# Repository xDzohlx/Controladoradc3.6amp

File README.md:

# Controladoradc3.6amp
Controladora electronica de velocidad de 3.6 amperios hasta 25 volts V1.1
Controladora electronica de velocidad de 3.6 amperios hasta 25 volts V1.1 Esta es la versión 1.1 de la tarjeta controladora fue diseñada por Carlos Vega, la selección de componentes del driver y el microcontrolador por Aldo Bucio. Está basada en otra paca diseñada por Aldo bucio hace tiempo. Perdí el primer archivo de la placa pero estan los archivos gerber pero estan los de la version 1.1.

Especificaciones: 4 celdas de litio polímero, hasta 25 volts absolutos(por los capacitores de puede aumentar la tensión hasta 32 volts absolutos limitados por el regulador) 3.6 amperios por canal, protegida para más corriente se apaga y reinicia cuando se alcanza esta corriente. El driver de los motores es muy confiable y a prueba de balas lo que se necesita para el combate de robots Canales completamente mezclados para conducir un robot en modo diferencial. Se leen dos canales de pwm en cualquier protocolo de envío de 50 a 100 hz. También esta la version de firmware con lectura de ppm en un solo cable con decodificador de un canal para la activación de un servo u otro actuador. Los esquematicos y la placa estan diseñadas en Eagle.Fue programada en atmel studio 7 con el microcontrolador Attiny828.

Manual de operacion Caracteristicas

Gracias por usar la tarjeta controladora electrónica de velocidad. Características: Canal doble 3.6 A por canal Protección contra sobre corriente y sobre temperatura 2-6s de litio polímero 25 volts absolutos 7.2 Amp Canal doble Interfaz RC PWM, PPM Decodificador en modo PPM sin retraso. Canales mezclados o bidireccionales. Sin retraso de señal de radio Auto calibración al encendido BEC conmutada de alta eficiencia 88% 1 A hasta 2A continuos. (BEC) Respuesta lineal Adelante y atrás a máxima potencia. PWM de 32 Khz Freno del motor Tiempo de servicio muy largo puede estar encendida por más de 1 hr. Conector JST para batería. Conectores de servo para señales.

El modo de operación viene preprogramdo, como lectura independiente de PWM, PPM, mezclados, bidireccionales o canal sencillo de mayor corriente estos modos son el firmware de la controladora. Modo PWM. El canal 1 es el volate y el canal 2 es el acelerador, el primero controla los giros mientras que el segundo controla el acelerador y la reversa. Modo PPM. En el canal 1 se conecta la señal PPM, el canal 1 es el volante y el canal 2 es el acelerador. El cable del canal dos es un decodificador del canal 3. En cualquiera de los modos cuenta con auto calibración al encendido por lo que se tiene que dar un tiempo a esto de 5 segundos antes de mover cualquier valor del radiocontrol. El led muestra el estado de la controladora.
Un video probando la tarjeta: https://t.co/X4io4Tz9yK?amp=1

Otros videos arreglando issues:
https://youtube.com/live/U84N-yGLdbo?feature=share

https://youtube.com/live/5lfUKTcOBrQ?feature=share

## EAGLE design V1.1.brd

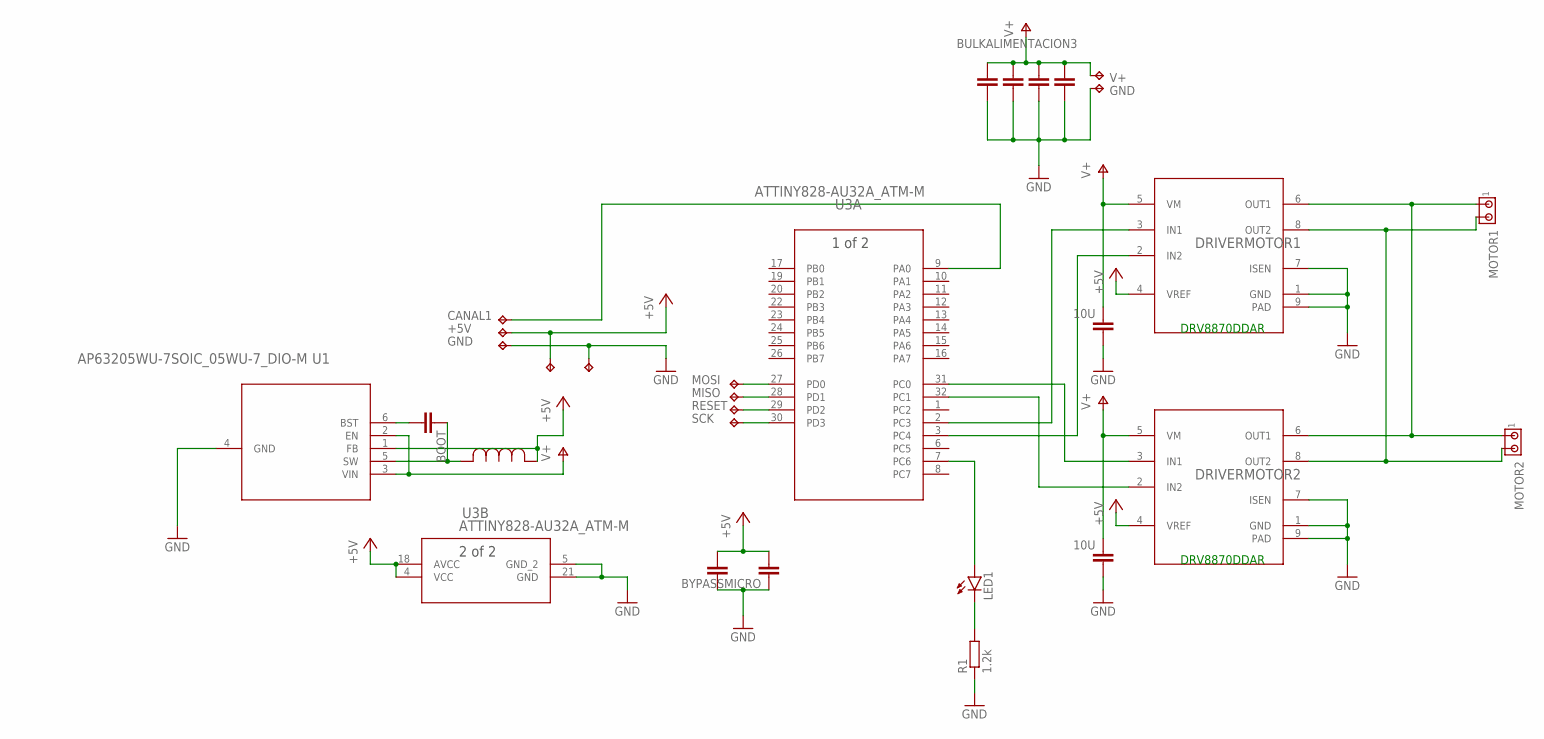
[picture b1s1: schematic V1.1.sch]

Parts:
BOOT: C-EUC0402; C0402
BULKALIMENTACION, BULKALIMENTACION1, BULKALIMENTACION2, BULKALIMENTACION3: C-EUC1206; C1206
BYPASS1: 10U; C0603
BYPASSMICRO, BYPASSMICRO2: C-EUC0603; C0603
BYPASSMOTOR2: 10U; C0603
DRIVERMOTOR1, DRIVERMOTOR2: DRV8870; DDA0008H_N
GND: TPTP20SQ; TP20SQ
LED1: LEDCHIPLED_0603; CHIPLED_0603
MISO: TPTP12R; TP12R
MOTOR1, MOTOR2: MTA02-100; 10X02MTA
R1: 1.2k; R0603
TP1, TP3, TP4, TP5, TP9: TPTP13SQ; TP13SQ
TP6, TP7, TP8: TPTP12R; TP12R
U1: AP63205WU-7SOIC_05WU-7_DIO-M; SOIC_05WU-7_DIO-M
U3: ATTINY828-AU32A_ATM-M; 32A_ATM-M
U$2: INDUCTOR4.7; IND_NRS5030T100MMGJ_TAY
V+: TPTP20SQ; TP20SQ

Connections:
+5V: BYPASSMICRO.2, BYPASSMICRO2.2, DRIVERMOTOR1.4 (VREF), DRIVERMOTOR2.4 (VREF), TP3.TP, TP9.TP, U1.1 (FB), U3.4 (VCC), U3.18 (AVCC), U$2.1
CANAL1: TP1.TP, U3.9 (PA0)
GND: BULKALIMENTACION.2, BULKALIMENTACION1.2, BULKALIMENTACION2.2, BULKALIMENTACION3.2, BYPASS1.1, BYPASSMICRO.1, BYPASSMICRO2.1, BYPASSMOTOR2.1, DRIVERMOTOR1.1 (GND), DRIVERMOTOR1.7 (ISEN), DRIVERMOTOR1.9 (PAD), DRIVERMOTOR2.1 (GND), DRIVERMOTOR2.7 (ISEN), DRIVERMOTOR2.9 (PAD), GND.TP, R1.1, TP4.TP, TP5.TP, U1.4 (GND), U3.5 (GND_2), U3.21 (GND)
MISO: TP6.TP, U3.28 (PD1)
MOSI: MISO.TP, U3.27 (PD0)
unnamed: DRIVERMOTOR1.3 (IN1), U3.2 (PC3)
unnamed: DRIVERMOTOR1.2 (IN2), U3.3 (PC4)
unnamed: DRIVERMOTOR2.3 (IN1), U3.31 (PC0)
unnamed: DRIVERMOTOR2.2 (IN2), U3.32 (PC1)
unnamed: DRIVERMOTOR1.8 (OUT2), DRIVERMOTOR2.8 (OUT2), MOTOR1.2, MOTOR2.2
unnamed: DRIVERMOTOR1.6 (OUT1), DRIVERMOTOR2.6 (OUT1), MOTOR1.1, MOTOR2.1
unnamed: LED1.A, U3.7 (PC6)
unnamed: LED1.C, R1.2
unnamed: BOOT.1, U1.5 (SW), U$2.2
unnamed: BOOT.2, U1.6 (BST)
RESET: TP7.TP, U3.29 (PD2)
SCK: TP8.TP, U3.30 (PD3)
V+: BULKALIMENTACION.1, BULKALIMENTACION1.1, BULKALIMENTACION2.1, BULKALIMENTACION3.1, BYPASS1.2, BYPASSMOTOR2.2, DRIVERMOTOR1.5 (VM), DRIVERMOTOR2.5 (VM), U1.2 (EN), U1.3 (VIN), V+.TP

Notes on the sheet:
DRV8870DDAR

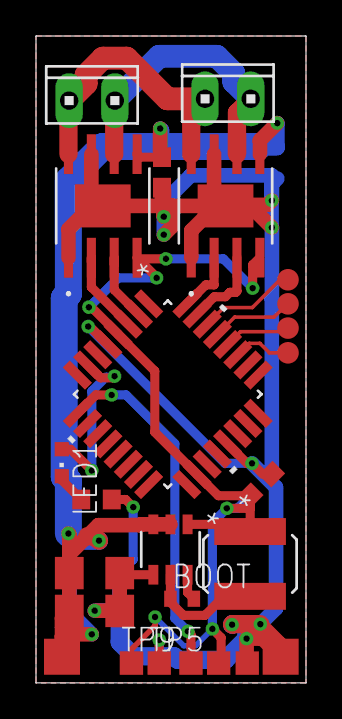
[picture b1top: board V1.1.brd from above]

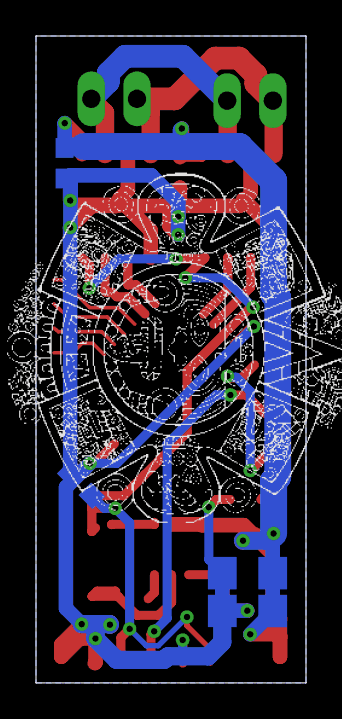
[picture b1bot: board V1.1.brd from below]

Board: 2 copper layers, 15.0 x 35.9 mm, 29 parts (4 on the bottom side), 18 nets.

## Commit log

2020-08-04 Lecutura y mezclado de dos canales
    Este es el codigo original donde se leen dos canales de pwm de rc y se mezclan, se mandan señales de pwm para el control de dos motores
2020-08-04 PPM
    Este codigo puede leer hasta 6 canales de PPM de rc, mezcla dos canales y manda por pwm señal para control de dos motores
2020-08-04 PWM
    Lee y mezcla dos canales de pwm para mandar señal de pwm para control de motores
2020-08-04 Update LICENSE
2020-08-10 Add files via upload
    se agrego pwm al led que muestra que no solo esta encendía sino que esta funcionando
2020-08-10 V1.2
    El esquemático es el mismo, la placa tiene mejores tolerancias, mejor distribución nuevos pads para señales y cumple con las especificaciones de jlcpcb
2020-08-11 Prueba de parpadeo led
    Ya se probo el nuevo firmware, me asuste porque pense que habia quemado la placa pero recuerden la configuración de los fusibles o habia hecho en una nueva placa con los fusibles de fabrica pero ya f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
2020-08-11 Hex file
2020-08-22 codigo para sbus
    Codigo propuesto para sbus falta probar
2020-08-22 Update main.cpp
    Es mejor probado pero al parecer la velocidad es mucha para el microcontrolador, lo menos que se tardar en entrar a la interrupción y poner un pin bajo es 8 u seg mientras que el ancho de pulso del s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
2020-08-22 Add files via upload
    Medición del tiempo de interrupción del osciloscopio tipico 10 useg lo menos que medi fueron 8 useg
2020-10-07 Create images
2021-01-03 Update main.cpp
    Agregue el decodificador de ppm para una salida
2021-04-03 Version mezcla
    Programacion de esc mezclada en c++
2023-05-22 Update README.md
    Agregue videos arreglando issues

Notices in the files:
parts and their libraries:
COPYRIGHT: Copyright (C) 2018 Accelerated Designs. All rights reserved
